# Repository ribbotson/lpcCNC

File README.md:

# lpcCNC Smoothieboard Derivative for CNC applications

This free open source derivative of the Smoothieboard is designed for CNC applications. It is intended for use with external stepper motor drivers. It features 13 digital open collector outputs, 8 digital inputs, 4 analog inputs, RS485 interface for spindle, 10V analog output for spindle, support for LCD screen, Ethernet, and power supply up to 40V.

## Content

This is a hardware project with PCB design file in Eagle. A 3D printable case ([Top]( http://a360.co/2vPnznS), [Bottom](http://a360.co/2j534xu)) design in Fusion360 is also provided. Example configuration files for Smoothieware and grbl-lpc are also provided.

## Authors

* **Richard Ibbotson**  

## License

Licensed under CERN OHL v.1.2 or later https://www.ohwr.org/documents/294 No warranty is provided for this documentation implied or otherwise.

## Acknowledgments

* All the folks at [rLab](http://www.rlab.org.uk) Reading Hackspace especially Toby
+ The Smoothieboard creators and the [Smoothieware](http://smoothieware.org/) team

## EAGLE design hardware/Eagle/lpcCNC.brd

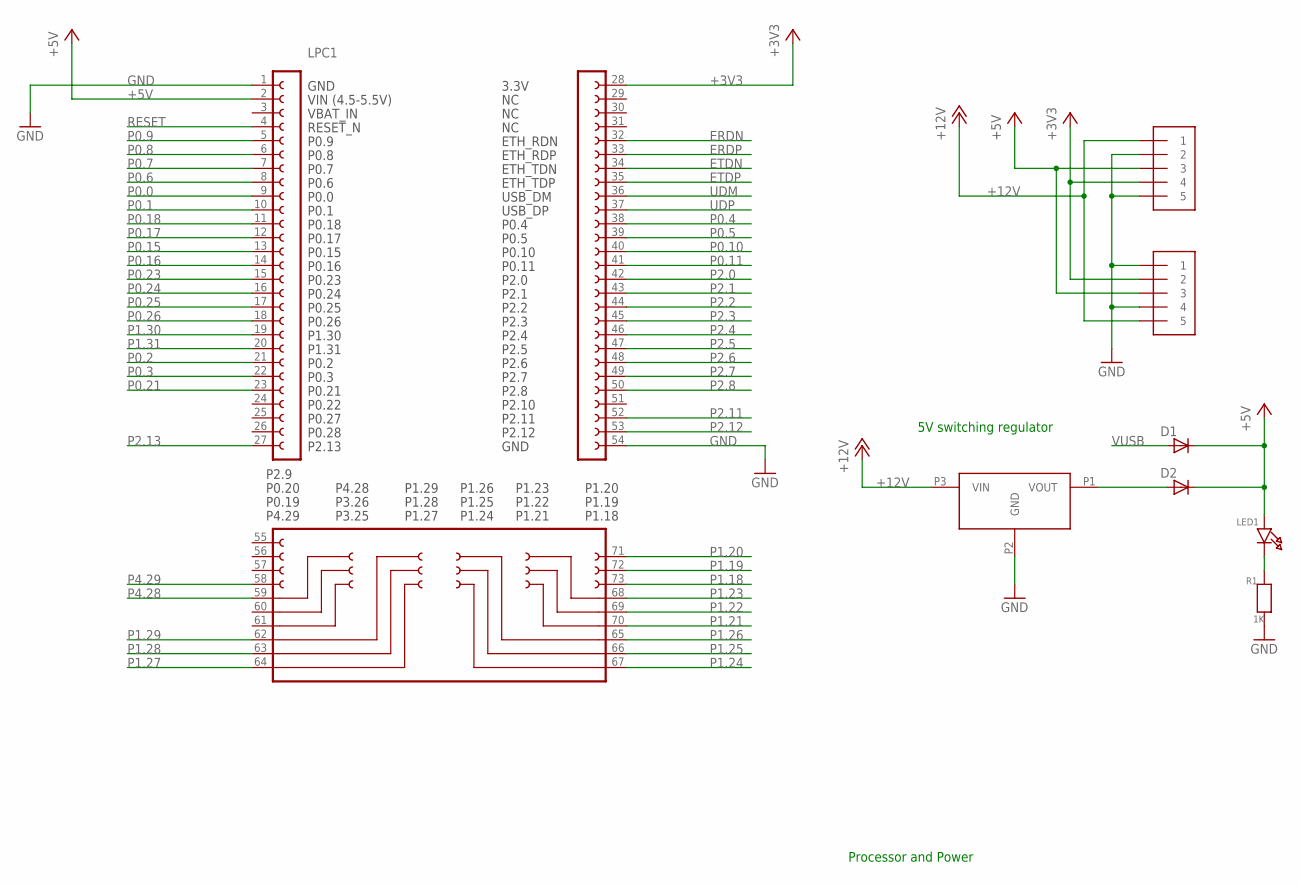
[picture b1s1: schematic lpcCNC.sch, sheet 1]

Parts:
D1, D2: DIODE-DO-214AC; DO-214AC
J1, J2: 1X5; 1X05-3.5MM
LED1: LED0603; CHIPLED_0603
LPC1: LPCXPRESSO_LPC1769
R1: 1K; 0603
VR1: 78SR

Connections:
+3V3: J1.4, J2.2, LPC1.28; also elsewhere on the board
+5V: D1.C, D2.C, J1.3, J2.3, LED1.A, LPC1.2; also elsewhere on the board
+12V: J1.1, J2.5, VR1.P3 (VIN); also elsewhere on the board
ERDN: LPC1.32; also elsewhere on the board
ERDP: LPC1.33; also elsewhere on the board
ETDN: LPC1.34; also elsewhere on the board
ETDP: LPC1.35; also elsewhere on the board
GND: J1.2, J1.5, J2.1, J2.4, LPC1.1, LPC1.54, R1.1, VR1.P2 (GND); also elsewhere on the board
unnamed: D2.A, VR1.P1 (VOUT)
unnamed: LED1.C, R1.2
P0.0: LPC1.9; also elsewhere on the board
P0.1: LPC1.10; also elsewhere on the board
P0.2: LPC1.21; also elsewhere on the board
P0.3: LPC1.22; also elsewhere on the board
P0.4: LPC1.38; also elsewhere on the board
P0.5: LPC1.39; also elsewhere on the board
P0.6: LPC1.8; also elsewhere on the board
P0.7: LPC1.7; also elsewhere on the board
P0.8: LPC1.6; also elsewhere on the board
P0.9: LPC1.5; also elsewhere on the board
P0.10: LPC1.40; also elsewhere on the board
P0.11: LPC1.41; also elsewhere on the board
P0.15: LPC1.13; also elsewhere on the board
P0.16: LPC1.14; also elsewhere on the board
P0.17: LPC1.12; also elsewhere on the board
P0.18: LPC1.11; also elsewhere on the board
P0.21: LPC1.23; also elsewhere on the board
P0.23: LPC1.15; also elsewhere on the board
P0.24: LPC1.16; also elsewhere on the board
P0.25: LPC1.17; also elsewhere on the board
P0.26: LPC1.18; also elsewhere on the board
P1.18: LPC1.73; also elsewhere on the board
P1.19: LPC1.72; also elsewhere on the board
P1.20: LPC1.71; also elsewhere on the board
P1.21: LPC1.70; also elsewhere on the board
P1.22: LPC1.69; also elsewhere on the board
P1.23: LPC1.68; also elsewhere on the board
P1.24: LPC1.67; also elsewhere on the board
P1.25: LPC1.66; also elsewhere on the board
P1.26: LPC1.65; also elsewhere on the board
P1.27: LPC1.64; also elsewhere on the board
P1.28: LPC1.63; also elsewhere on the board
P1.29: LPC1.62; also elsewhere on the board
P1.30: LPC1.19; also elsewhere on the board
P1.31: LPC1.20; also elsewhere on the board
P2.0: LPC1.42; also elsewhere on the board
P2.1: LPC1.43; also elsewhere on the board
P2.2: LPC1.44; also elsewhere on the board
P2.3: LPC1.45; also elsewhere on the board
P2.4: LPC1.46; also elsewhere on the board
P2.5: LPC1.47; also elsewhere on the board
P2.6: LPC1.48; also elsewhere on the board
P2.7: LPC1.49; also elsewhere on the board
P2.8: LPC1.50; also elsewhere on the board
P2.11: LPC1.52; also elsewhere on the board
P2.12: LPC1.53; also elsewhere on the board
P2.13: LPC1.27; also elsewhere on the board
P4.28: LPC1.59; also elsewhere on the board
P4.29: LPC1.58; also elsewhere on the board
RESET: LPC1.4; also elsewhere on the board
UDM: LPC1.36; also elsewhere on the board
UDP: LPC1.37; also elsewhere on the board
VUSB: D1.A; also elsewhere on the board

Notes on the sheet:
Processor and Power
5V switching regulator

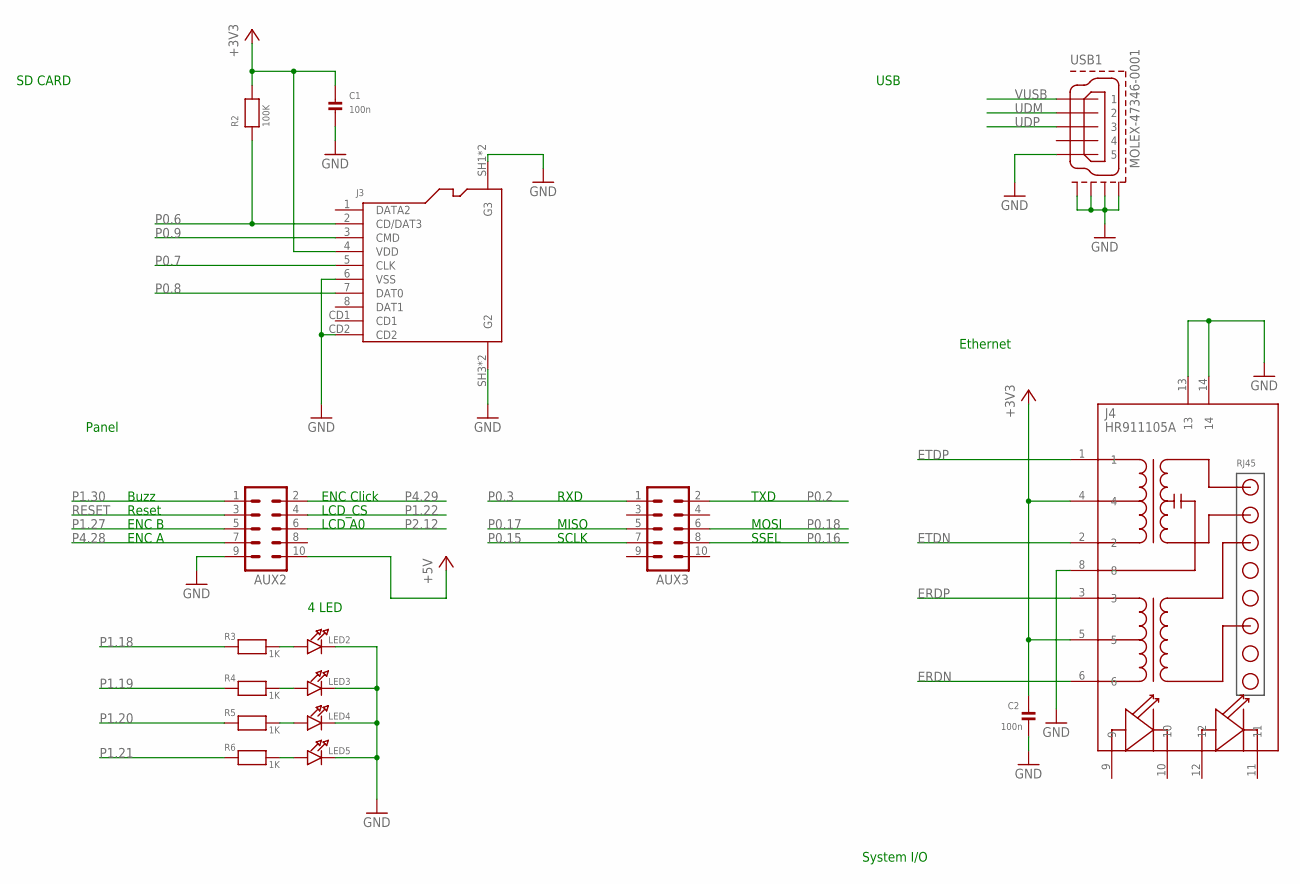
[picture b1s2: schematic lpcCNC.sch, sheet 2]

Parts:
AUX2, AUX3: ML10
C1, C2: 100n; 0603
J3: AMPHENOL_114-00841-68
J4: HR911105A
LED2, LED3, LED4, LED5: LED0603; CHIPLED_0603
R2: 100K; 0603
R3, R4, R5, R6: 1K; 0603
USB1: MOLEX-47346-0001; MOLEX-47364-0001

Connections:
+3V3: C1.1, C2.1, J3.4 (VDD), J4.4, J4.5, R2.2; also elsewhere on the board
+5V: AUX2.10; also elsewhere on the board
ERDN: J4.6; also elsewhere on the board
ERDP: J4.3; also elsewhere on the board
ETDN: J4.2; also elsewhere on the board
ETDP: J4.1; also elsewhere on the board
GND: AUX2.9, C1.2, C2.2, J3.6 (VSS), J3.CD2, J3.SH1 (G3), J3.SH2 (G3), J3.SH3 (G2), J3.SH4 (G2), J4.8, J4.13, J4.14, LED2.C, LED3.C, LED4.C, LED5.C, USB1.5, USB1.GND1, USB1.GND2, USB1.GND3, USB1.GND4; also elsewhere on the board
unnamed: LED2.A, R3.2
unnamed: LED3.A, R4.2
unnamed: LED4.A, R5.2
unnamed: LED5.A, R6.2
P0.2: AUX3.2; also elsewhere on the board
P0.3: AUX3.1; also elsewhere on the board
P0.6: J3.2 (CD/DAT3), R2.1; also elsewhere on the board
P0.7: J3.5 (CLK); also elsewhere on the board
P0.8: J3.7 (DAT0); also elsewhere on the board
P0.9: J3.3 (CMD); also elsewhere on the board
P0.15: AUX3.7; also elsewhere on the board
P0.16: AUX3.8; also elsewhere on the board
P0.17: AUX3.5; also elsewhere on the board
P0.18: AUX3.6; also elsewhere on the board
P1.18: R3.1; also elsewhere on the board
P1.19: R4.1; also elsewhere on the board
P1.20: R5.1; also elsewhere on the board
P1.21: R6.1; also elsewhere on the board
P1.22: AUX2.4; also elsewhere on the board
P1.27: AUX2.5; also elsewhere on the board
P1.30: AUX2.1; also elsewhere on the board
P2.12: AUX2.6; also elsewhere on the board
P4.28: AUX2.7; also elsewhere on the board
P4.29: AUX2.2; also elsewhere on the board
RESET: AUX2.3; also elsewhere on the board
UDM: USB1.2; also elsewhere on the board
UDP: USB1.3; also elsewhere on the board
VUSB: USB1.1; also elsewhere on the board

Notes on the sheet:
System I/O
Ethernet
USB
SD CARD
Panel
4 LED
ENC Click
LCD_CS
LCD A0
Reset
ENC A
ENC B
Buzz
TXD
RXD
MISO
SCLK
MOSI
SSEL

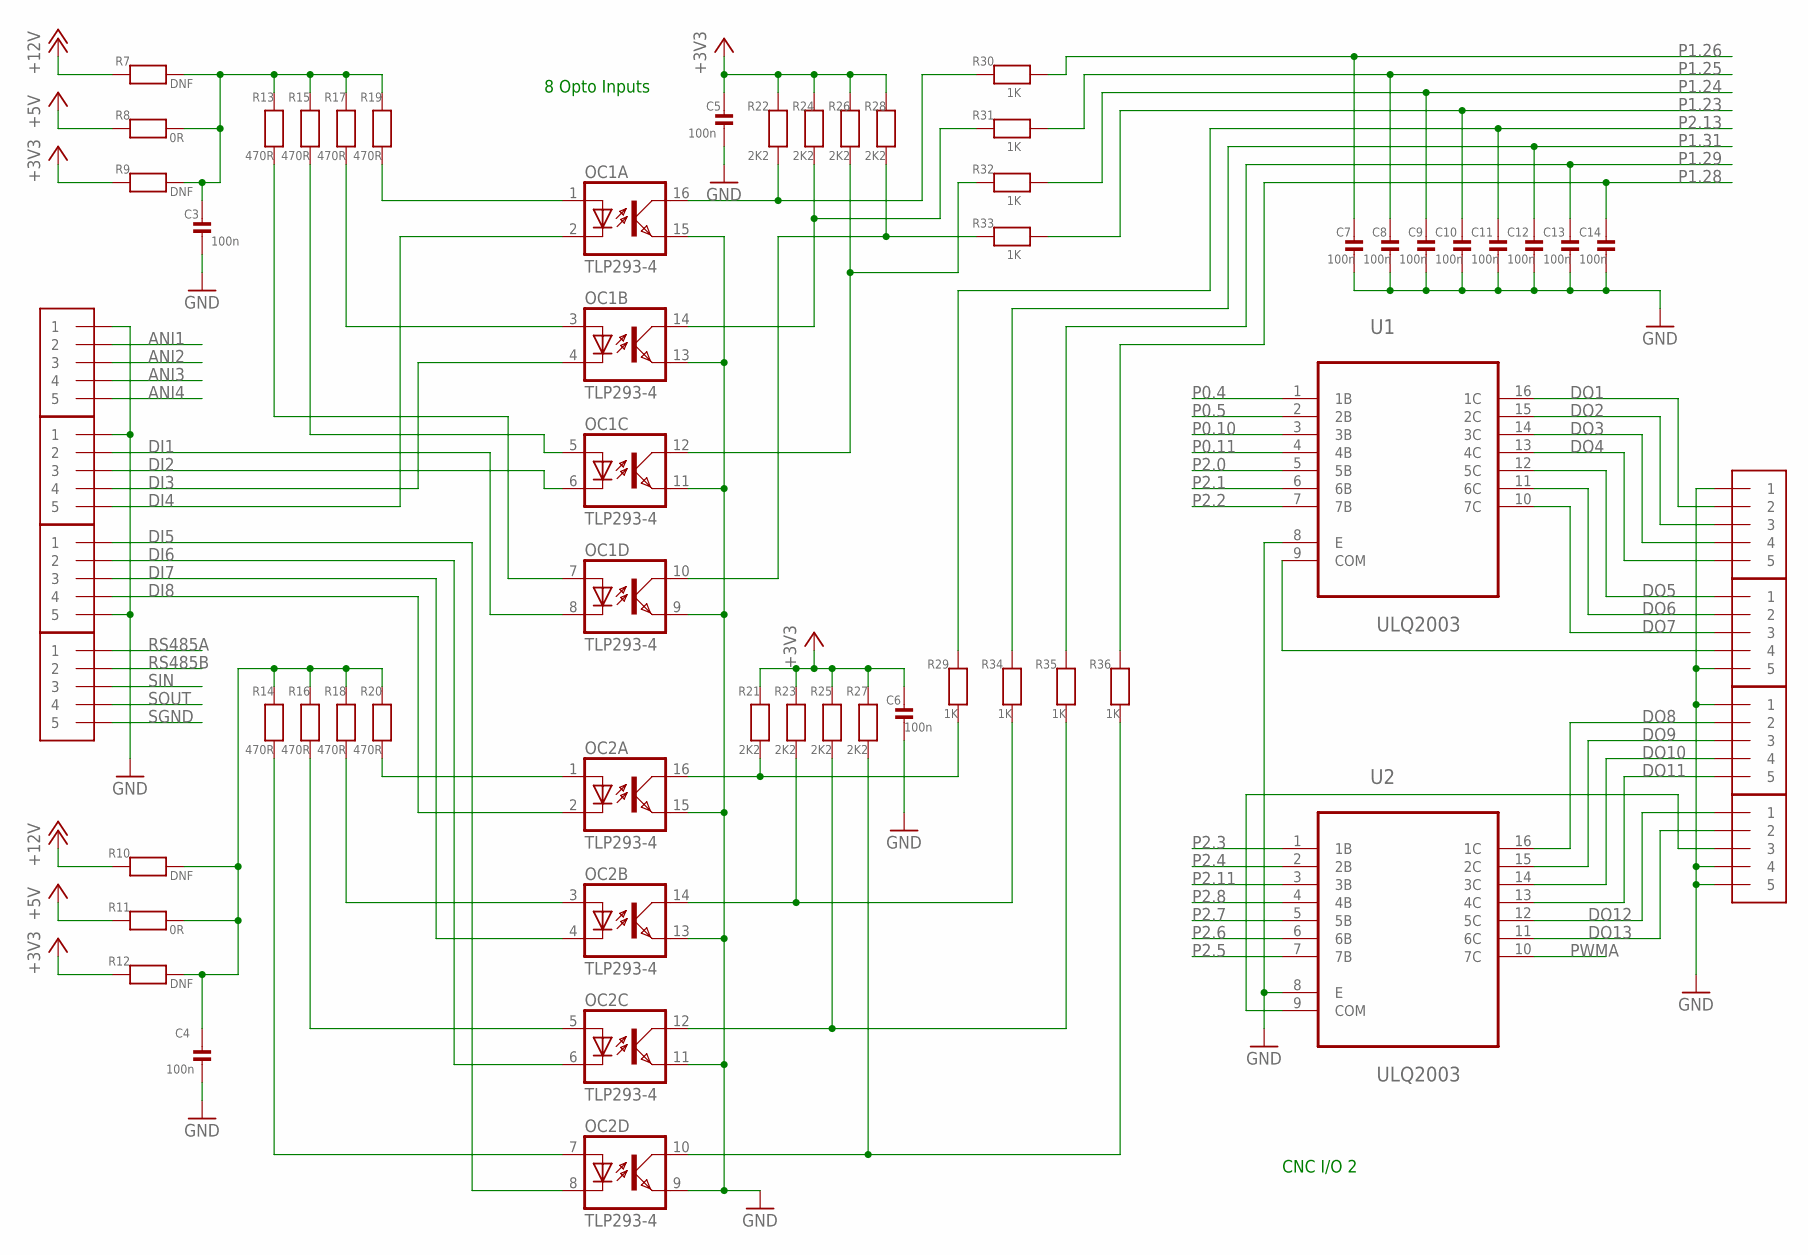
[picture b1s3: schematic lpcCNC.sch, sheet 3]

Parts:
C3, C4, C5, C6, C7, C8, C9, C10, C11, C12, C13, C14: 100n; 0603
J5, J6, J7, J8, J9, J10, J11, J12: 1X5; 1X05-3.5MM
OC1, OC2: TLP293-4; MINI-FLAT-16
R7, R9, R10, R12: DNF; 0603
R8, R11: 0R; 0603
R13, R14, R15, R16, R17, R18, R19, R20: 470R; 0603
R21, R22, R23, R24, R25, R26, R27, R28: 2K2; 0603
R29, R30, R31, R32, R33, R34, R35, R36: 1K; 0603
U1, U2: ULQ2003; SOIC127P600X175-16N

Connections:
+3V3: C5.1, C6.1, R9.2, R12.2, R21.2, R22.2, R23.2, R24.2, R25.2, R26.2, R27.2, R28.2; also elsewhere on the board
+5V: R8.2, R11.2; also elsewhere on the board
+12V: R7.2, R10.2; also elsewhere on the board
ANI1: J5.2; also elsewhere on the board
ANI2: J5.3; also elsewhere on the board
ANI3: J5.4; also elsewhere on the board
ANI4: J5.5; also elsewhere on the board
DI1: J6.2, OC1.8 (C)
DI2: J6.3, OC1.6 (C)
DI3: J6.4, OC1.4 (C)
DI4: J6.5, OC1.2 (C)
DI5: J7.1, OC2.8 (C)
DI6: J7.2, OC2.6 (C)
DI7: J7.3, OC2.4 (C)
DI8: J7.4, OC2.2 (C)
DO1: J9.2, U1.16 (1C)
DO2: J9.3, U1.15 (2C)
DO3: J9.4, U1.14 (3C)
DO4: J9.5, U1.13 (4C)
DO5: J10.1, U1.12 (5C)
DO6: J10.2, U1.11 (6C)
DO7: J10.3, U1.10 (7C)
DO8: J11.2, U2.16 (1C)
DO9: J11.3, U2.15 (2C)
DO10: J11.4, U2.14 (3C)
DO11: J11.5, U2.13 (4C)
DO12: J12.1, U2.12 (5C)
DO13: J12.2, U2.11 (6C)
GND: C3.2, C4.2, C5.2, C6.2, C7.2, C8.2, C9.2, C10.2, C11.2, C12.2, C13.2, C14.2, J5.1, J6.1, J7.5, J9.1, J10.5, J11.1, J12.4, J12.5, OC1.9 (EMIT), OC1.11 (EMIT), OC1.13 (EMIT), OC1.15 (EMIT), OC2.9 (EMIT), OC2.11 (EMIT), OC2.13 (EMIT), OC2.15 (EMIT), U1.8 (E), U2.8 (E); also elsewhere on the board
unnamed: J10.4, U1.9 (COM)
unnamed: J12.3, U2.9 (COM)
unnamed: C3.1, R7.1, R8.1, R9.1, R13.2, R15.2, R17.2, R19.2
unnamed: OC2.1 (A), R20.1
unnamed: OC2.3 (A), R18.1
unnamed: OC2.5 (A), R16.1
unnamed: OC2.7 (A), R14.1
unnamed: C4.1, R10.1, R11.1, R12.1, R14.2, R16.2, R18.2, R20.2
unnamed: OC1.1 (A), R19.1
unnamed: OC1.3 (A), R17.1
unnamed: OC1.5 (A), R15.1
unnamed: OC1.7 (A), R13.1
unnamed: OC1.16 (COL), R22.1, R30.2
unnamed: OC1.14 (COL), R24.1, R31.2
unnamed: OC2.16 (COL), R21.1, R29.1
unnamed: OC2.14 (COL), R23.1, R34.1
unnamed: OC2.12 (COL), R25.1, R35.1
unnamed: OC2.10 (COL), R27.1, R36.1
unnamed: OC1.12 (COL), R26.1, R32.2
unnamed: OC1.10 (COL), R28.1, R33.2
P0.4: U1.1 (1B); also elsewhere on the board
P0.5: U1.2 (2B); also elsewhere on the board
P0.10: U1.3 (3B); also elsewhere on the board
P0.11: U1.4 (4B); also elsewhere on the board
P1.23: C10.1, R33.1; also elsewhere on the board
P1.24: C9.1, R32.1; also elsewhere on the board
P1.25: C8.1, R31.1; also elsewhere on the board
P1.26: C7.1, R30.1; also elsewhere on the board
P1.28: C14.1, R36.2; also elsewhere on the board
P1.29: C13.1, R35.2; also elsewhere on the board
P1.31: C12.1, R34.2; also elsewhere on the board
P2.0: U1.5 (5B); also elsewhere on the board
P2.1: U1.6 (6B); also elsewhere on the board
P2.2: U1.7 (7B); also elsewhere on the board
P2.3: U2.1 (1B); also elsewhere on the board
P2.4: U2.2 (2B); also elsewhere on the board
P2.5: U2.7 (7B); also elsewhere on the board
P2.6: U2.6 (6B); also elsewhere on the board
P2.7: U2.5 (5B); also elsewhere on the board
P2.8: U2.4 (4B); also elsewhere on the board
P2.11: U2.3 (3B); also elsewhere on the board
P2.13: C11.1, R29.2; also elsewhere on the board
PWMA: U2.10 (7C); also elsewhere on the board
RS485A: J8.1; also elsewhere on the board
RS485B: J8.2; also elsewhere on the board
SGND: J8.5; also elsewhere on the board
SIN: J8.3; also elsewhere on the board
SOUT: J8.4; also elsewhere on the board

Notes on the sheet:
CNC I/O 2
8 Opto Inputs

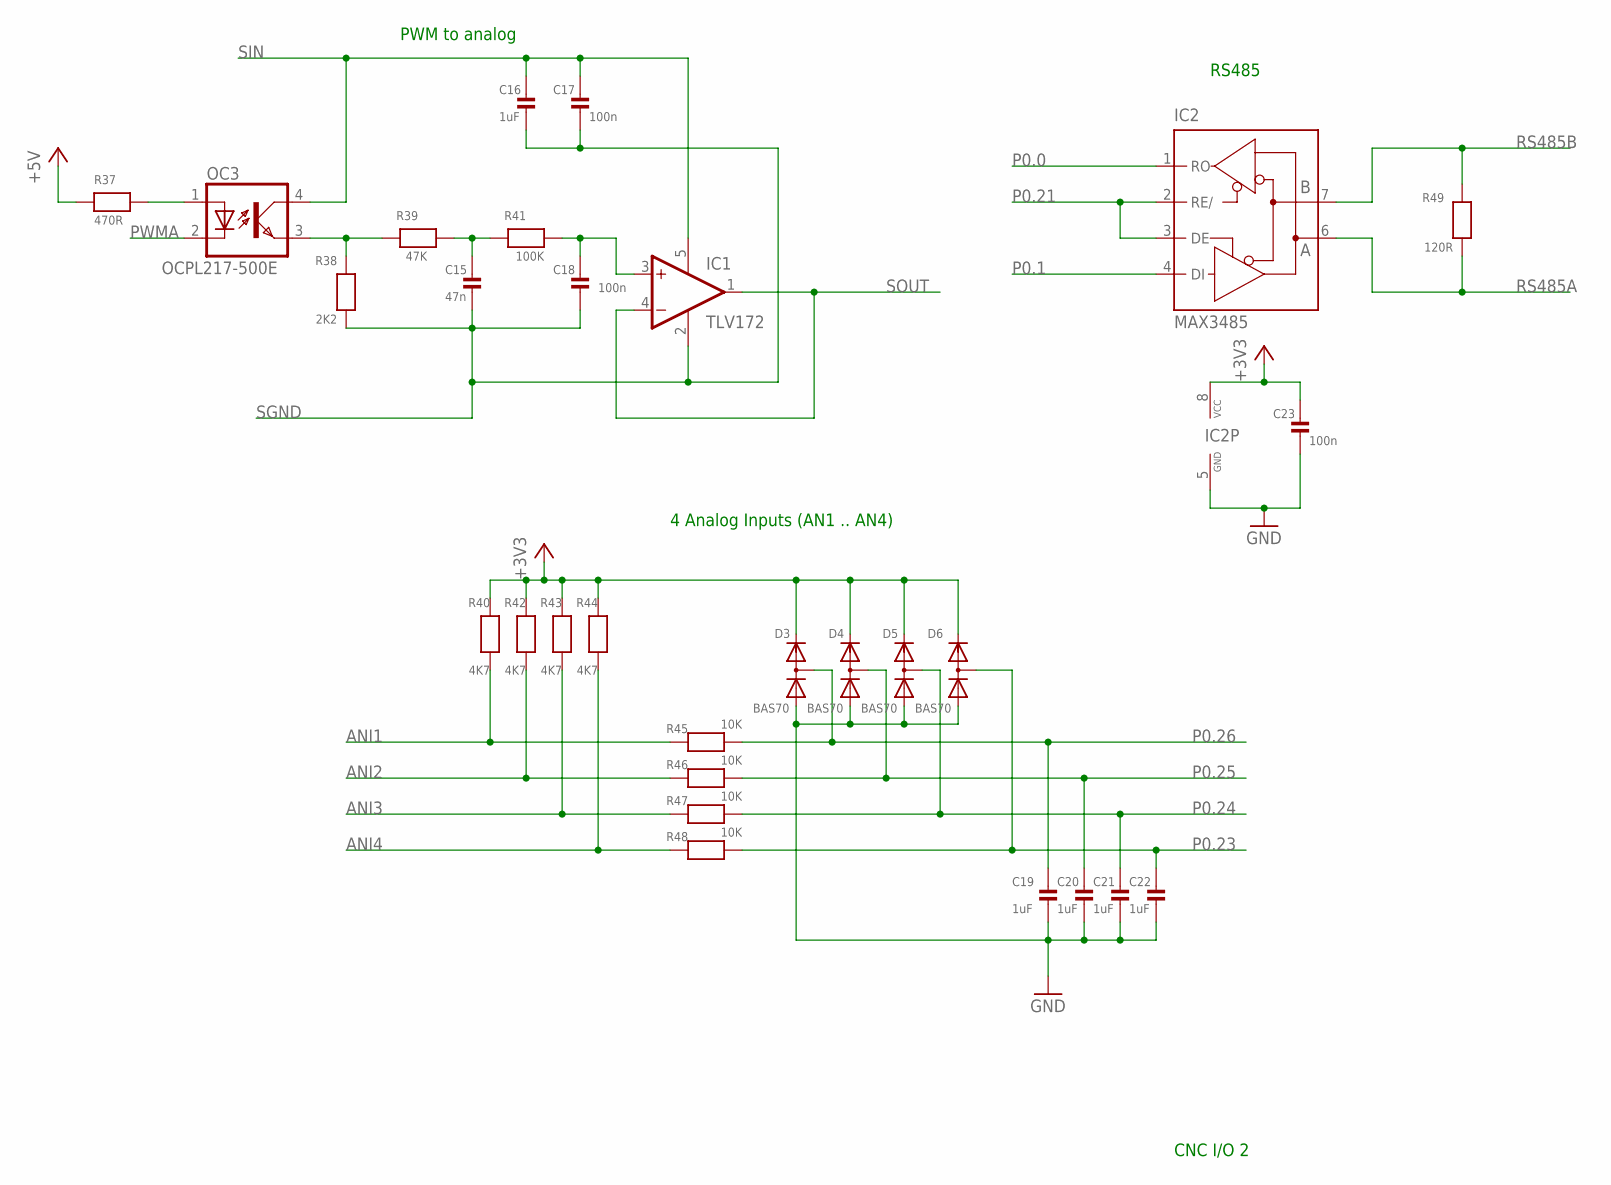
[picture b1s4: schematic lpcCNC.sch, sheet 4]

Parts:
C15: 47n; 0603
C16, C19, C20, C21, C22: 1uF; 0603
C17, C18, C23: 100n; 0603
D3, D4, D5, D6: BAS70; SOT23
IC1: TLV172; SOT23-5
IC2: MAX3485; SO08
OC3: OCPL217-500E; MINI-FLAT-4
R37: 470R; 0603
R38: 2K2; 0603
R39: 47K; 0603
R40, R42, R43, R44: 4K7; 0603
R41: 100K; 0603
R45, R46, R47, R48: 10K; 0603
R49: 120R; 0603

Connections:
+3V3: C23.1, D3.2 (C), D4.2 (C), D5.2 (C), D6.2 (C), IC2.8 (VCC), R40.2, R42.2, R43.2, R44.2; also elsewhere on the board
+5V: R37.1; also elsewhere on the board
ANI1: R40.1, R45.2; also elsewhere on the board
ANI2: R42.1, R46.2; also elsewhere on the board
ANI3: R43.1, R47.2; also elsewhere on the board
ANI4: R44.1, R48.2; also elsewhere on the board
GND: C19.2, C20.2, C21.2, C22.2, C23.2, D3.1 (A), D4.1 (A), D5.1 (A), D6.1 (A), IC2.5 (GND); also elsewhere on the board
unnamed: OC3.1 (A), R37.2
unnamed: OC3.3 (EMIT), R38.2, R39.2
unnamed: C15.1, R39.1, R41.2
unnamed: C18.1, IC1.3 (+IN), R41.1
P0.0: IC2.1 (RO); also elsewhere on the board
P0.1: IC2.4 (DI); also elsewhere on the board
P0.21: IC2.2 (RE/), IC2.3 (DE); also elsewhere on the board
P0.23: C22.1, D6.3 (AC), R48.1; also elsewhere on the board
P0.24: C21.1, D5.3 (AC), R47.1; also elsewhere on the board
P0.25: C20.1, D4.3 (AC), R46.1; also elsewhere on the board
P0.26: C19.1, D3.3 (AC), R45.1; also elsewhere on the board
PWMA: OC3.2 (C); also elsewhere on the board
RS485A: IC2.6 (A), R49.1; also elsewhere on the board
RS485B: IC2.7 (B), R49.2; also elsewhere on the board
SGND: C15.2, C16.2, C17.2, C18.2, IC1.2 (V-), R38.1; also elsewhere on the board
SIN: C16.1, C17.1, IC1.5 (V+), OC3.4 (COL); also elsewhere on the board
SOUT: IC1.1 (OUT), IC1.4 (-IN); also elsewhere on the board

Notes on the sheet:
CNC I/O 2
4 Analog Inputs (AN1 .. AN4)
PWM to analog
RS485

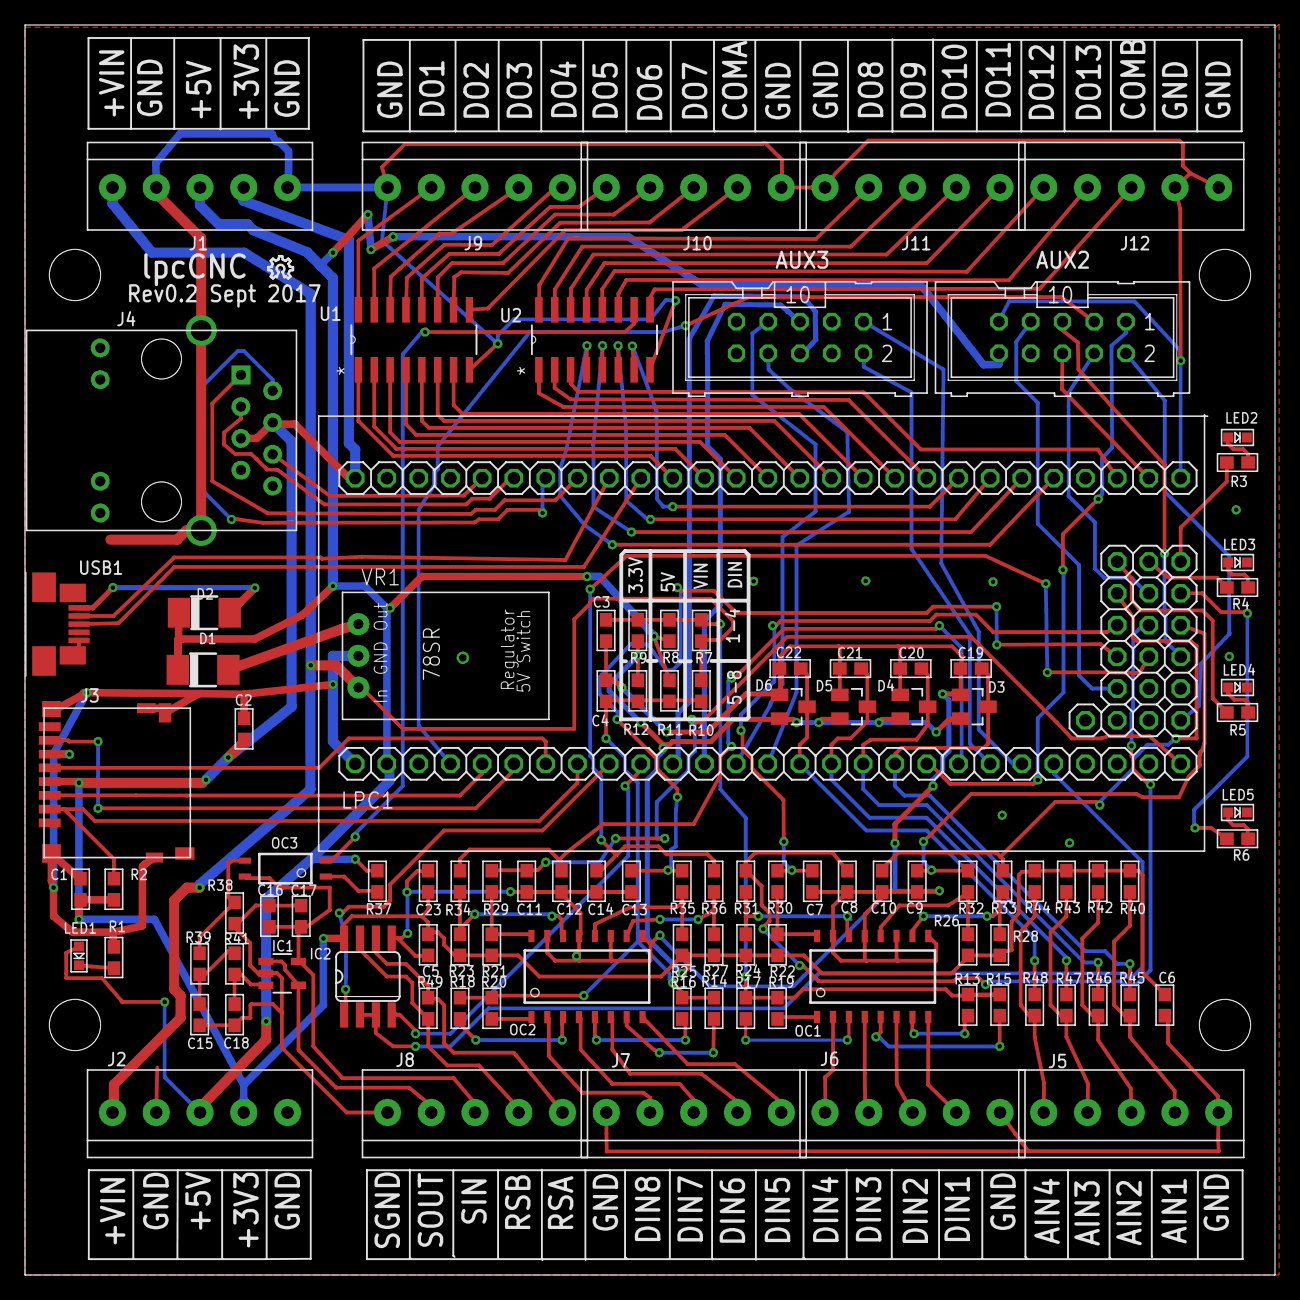
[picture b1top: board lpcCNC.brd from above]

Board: 2 copper layers, 100.0 x 100.0 mm, 108 parts (0 on the bottom side), 122 nets.

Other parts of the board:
U$1: OSHW_8X70_NOTEXT

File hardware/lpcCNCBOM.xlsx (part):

Column1 | Column2 | Column3 | Column4 | Column5 | Column6 | Column7 | Column8 | Column9
Part | Value | Device | Package | Description | Manufacturer | Manufacturer Part Number | Supplier | Supplier Part number
AUX2 | 10 Way | Header | 10 Way | 10 Way Boxed Header | TruConnect | DS1013-10 | Rapid | 19-0033
AUX3 | 10 Way | Header | ML10 | 10 Way Boxed Header | TruConnect | DS1013-10 | Rapid | 19-0033
C1 | 100n | Cap Ceramic 50V | 0603 | Ceramic Capacitors | Murata | GRM188F51H104ZA01D | RS | 723-5534
C2 | 100n | Cap Ceramic 50V | 0603 | Ceramic Capacitors | Murata | GRM188F51H104ZA01D | RS | 723-5534
C3 | 100n | Cap Ceramic 50V | 0603 | Ceramic Capacitors | Murata | GRM188F51H104ZA01D | RS | 723-5534
C4 | 100n | Cap Ceramic 50V | 0603 | Ceramic Capacitors | Murata | GRM188F51H104ZA01D | RS | 723-5534
C5 | 100n | Cap Ceramic 50V | 0603 | Ceramic Capacitors | Murata | GRM188F51H104ZA01D | RS | 723-5534
C6 | 100n | Cap Ceramic 50V | 0603 | Ceramic Capacitors | Murata | GRM188F51H104ZA01D | RS | 723-5534
C7 | 100n | Cap Ceramic 50V | 0603 | Ceramic Capacitors | Murata | GRM188F51H104ZA01D | RS | 723-5534
C8 | 100n | Cap Ceramic 50V | 0603 | Ceramic Capacitors | Murata | GRM188F51H104ZA01D | RS | 723-5534
C9 | 100n | Cap Ceramic 50V | 0603 | Ceramic Capacitors | Murata | GRM188F51H104ZA01D | RS | 723-5534
C10 | 100n | Cap Ceramic 50V | 0603 | Ceramic Capacitors | Murata | GRM188F51H104ZA01D | RS | 723-5534
C11 | 100n | Cap Ceramic 50V | 0603 | Ceramic Capacitors | Murata | GRM188F51H104ZA01D | RS | 723-5534
C12 | 100n | Cap Ceramic 50V | 0603 | Ceramic Capacitors | Murata | GRM188F51H104ZA01D | RS | 723-5534
C13 | 100n | Cap Ceramic 50V | 0603 | Ceramic Capacitors | Murata | GRM188F51H104ZA01D | RS | 723-5534
C14 | 100n | Cap Ceramic 50V | 0603 | Ceramic Capacitors | Murata | GRM188F51H104ZA01D | RS | 723-5534
C15 | 47n | Cap Ceramic 50V | 0603 | Ceramic Capacitors | Murata | GRM188B11E473KA01D | RS | 798-0332
C16 | 1uF | Cap Ceramic 25V | 0603 | Ceramic Capacitors | Murata | GRM188R61E105KA12D | RS | 723-5587
C17 | 100n | Cap Ceramic 50V | 0603 | Ceramic Capacitors | Murata | GRM188F51H104ZA01D | RS | 723-5534
C18 | 100n | Cap Ceramic 50V | 0603 | Ceramic Capacitors | Murata | GRM188F51H104ZA01D | RS | 723-5534
C19 | 1uF | Cap Ceramic 25V | 0603 | Ceramic Capacitors | Murata | GRM188R61E105KA12D | RS | 723-5587
C20 | 1uF | Cap Ceramic 25V | 0603 | Ceramic Capacitors | Murata | GRM188R61E105KA12D | RS | 723-5587
C21 | 1uF | Cap Ceramic 25V | 0603 | Ceramic Capacitors | Murata | GRM188R61E105KA12D | RS | 723-5587
C22 | 1uF | Cap Ceramic 25V | 0603 | Ceramic Capacitors | Murata | GRM188R61E105KA12D | RS | 723-5587
C23 | 100n | Cap Ceramic 50V | 0603 | Ceramic Capacitors | Murata | GRM188F51H104ZA01D | RS | 723-5534
D1 | MBRA140 | DIODE-DO-214AC | DO-214AC | Schottky Power Diode | ON Semi | MBRA140T3G | RS | 625-5650
D2 | MBRA140 | DIODE-DO-214AC | DO-214AC | Schottky Power Diode | ON Semi | MBRA140T3G | RS | 625-5650
D3 | BAS70-04 | DIODE_2CACA-SOT23 | SOT23 | Dual Schottky Diode | Multicomp | BAS70-04 | Farnell | 179-7835
D4 | BAS70-04 | DIODE_2CACA-SOT23 | SOT23 | Dual Schottky Diode | Multicomp | BAS70-04 | Farnell | 179-7835
D5 | BAS70-04 | DIODE_2CACA-SOT23 | SOT23 | Dual Schottky Diode | Multicomp | BAS70-04 | Farnell | 179-7835
D6 | BAS70-04 | DIODE_2CACA-SOT23 | SOT23 | Dual Schottky Diode | Multicomp | BAS70-04 | Farnell | 179-7835
IC1 | TLV172 | TLV172MF | SOT23-5 | Low Power Single Op Amp | Texas Instruments | TLV172IDBVR | Farnell | 267-7088
IC2 | MAX3485 | MAX481CSA | SO08 | RS485 Transceiver | Maxim | MAX3485ECSA+ | Farnell | 251-8816
J1 | 1X5 | 1X5 | 1X05-3.5MM | 3.5mm Pitch Screw Header | CamdenBoss | CTB3051/5BK | Rapid | 21-4708
J2 | 1X5 | 1X5 | 1X05-3.5MM | 3.5mm Pitch Screw Header | CamdenBoss | CTB3051/5BK | Rapid | 21-4708
J3 |  | AMPHENOL_114-00841-68 | AMPHENOL_114-00841-68 | Micro SD Card Holder | Amphenol | 114-00841-68 | Farnell | 266-6772
J4 | HR911105A | HR911105A | HR911105A | Ethernet Mag Jack | HanRun | HR911105A | eBay | HR911105A
J5 | 1X5 | 1X5 | 1X05-3.5MM | 3.5mm Pitch Screw Header | CamdenBoss | CTB3051/5BK | Rapid | 21-4708
J6 | 1X5 | 1X5 | 1X05-3.5MM | 3.5mm Pitch Screw Header | CamdenBoss | CTB3051/5BK | Rapid | 21-4708
J7 | 1X5 | 1X5 | 1X05-3.5MM | 3.5mm Pitch Screw Header | CamdenBoss | CTB3051/5BK | Rapid | 21-4708
J8 | 1X5 | 1X5 | 1X05-3.5MM | 3.5mm Pitch Screw Header | CamdenBoss | CTB3051/5BK | Rapid | 21-4708
J9 | 1X5 | 1X5 | 1X05-3.5MM | 3.5mm Pitch Screw Header | CamdenBoss | CTB3051/5BK | Rapid | 21-4708
J10 | 1X5 | 1X5 | 1X05-3.5MM | 3.5mm Pitch Screw Header | CamdenBoss | CTB3051/5BK | Rapid | 21-4708
J11 | 1X5 | 1X5 | 1X05-3.5MM | 3.5mm Pitch Screw Header | CamdenBoss | CTB3051/5BK | Rapid | 21-4708
J12 | 1X5 | 1X5 | 1X05-3.5MM | 3.5mm Pitch Screw Header | CamdenBoss | CTB3051/5BK | Rapid | 21-4708
J13 | 27 pin | 2.54mm Pitch Female | Pin Header | Female Pin Header |  | 40 Pin strip | eBay
J14 | 27 pin | 2.54mm Pitch Female | Pin Header | Female Pin Header |  | 40 Pin strip | eBay
J15 | 4 pin | 2.54mm Pitch Female | Pin Header | Female Pin Header |  | 40 Pin strip | eBay
J16 | 3 pin | 2.54mm Pitch Female | Pin Header | Female Pin Header |  | 40 Pin strip | eBay
J17 | 3 pin | 2.54mm Pitch Female | Pin Header | Female Pin Header |  | 40 Pin strip | eBay
J18 | 3 pin | 2.54mm Pitch Female | Pin Header | Female Pin Header |  | 40 Pin strip | eBay
J19 | 27 pin | 2.54mm Pitch Male | Pin Header | Male Pin Header |  | 40 Pin strip | eBay
J20 | 27 pin | 2.54mm Pitch Male | Pin Header | Male Pin Header |  | 40 Pin strip | eBay
J21 | 4 pin | 2.54mm Pitch Male | Pin Header | Male Pin Header |  | 40 Pin strip | eBay
J22 | 3 pin | 2.54mm Pitch Male | Pin Header | Male Pin Header |  | 40 Pin strip | eBay
J23 | 3 pin | 2.54mm Pitch Male | Pin Header | Male Pin Header |  | 40 Pin strip | eBay
J24 | 3 pin | 2.54mm Pitch Male | Pin Header | Male Pin Header |  | 40 Pin strip | eBay
LED1 | Green |  | LED 0603 | SMT LED | Osram | LP L296-J2L2-25 | RS | 915-4768
LED2 | Green |  | LED 0603 | SMT LED | Osram | LP L296-J2L2-25 | RS | 915-4768
LED3 | Green |  | LED 0603 | SMT LED | Osram | LP L296-J2L2-25 | RS | 915-4768
LED4 | Green |  | LED 0603 | SMT LED | Osram | LP L296-J2L2-25 | RS | 915-4768
LED5 | Green |  | LED 0603 | SMT LED | Osram | LP L296-J2L2-25 | RS | 915-4768
LPC1 | LPC Expresso1769 | LPCXPRESSO_LPC1769 | Custom | Processor Module | NXP | OM13085UL | Farnell | 252-3091
OC1 | TLP293-4 | TLP293-4 | SOIC16 | Quad Optocoupler | Toshiba | TLP293-4 | Farnell | 252-4319
OC2 | TLP293-4 | TLP293-4 | SOIC16 | Quad Optocoupler | Toshiba | Toshiba | Farnell | 252-4319
OC3 | ACPL217-500E | ACPL217 | SOIC4 | Optocoupler | Avago | ACPL-217-500E | Rapid | 75-0230
R1 | 1K | RESISTOR0603 | 0603 | Resistors | Panasonic | ERJ3EKF1001V | RS | 873-9223
R2 | 100K | RESISTOR0603 | 0603 | Resistors | Panasonic | ERJU03F1003V | RS | 873-9220
R3 | 1K | RESISTOR0603 | 0603 | Resistors | Panasonic | ERJ3EKF1001V | RS | 873-9223
R4 | 1K | RESISTOR0603 | 0603 | Resistors | Panasonic | ERJ3EKF1001V | RS | 873-9223
R5 | 1K | RESISTOR0603 | 0603 | Resistors | Panasonic | ERJ3EKF1001V | RS | 873-9223
R6 | 1K | RESISTOR0603 | 0603 | Resistors | Panasonic | ERJ3EKF1001V | RS | 873-9223
R7 | Do Not Fit | RESISTOR0603 | 0603 | Resistors | Vishay | CRCW06030000Z0EB | RS | 678-9670
R8 | 0R | RESISTOR0603 | 0603 | Resistors | Vishay | CRCW06030000Z0EB | RS | 678-9670
R9 | Do Not Fit | RESISTOR0603 | 0603 | Resistors | Vishay | CRCW06030000Z0EB | RS | 678-9670
R10 | Do Not Fit | RESISTOR0603 | 0603 | Resistors | Vishay | CRCW06030000Z0EB | RS | 678-9670
R11 | 0R | RESISTOR0603 | 0603 | Resistors | Vishay | CRCW06030000Z0EB | RS | 678-9670
R12 | Do Not Fit | RESISTOR0603 | 0603 | Resistors | Vishay | CRCW06030000Z0EB | RS | 678-9670
R13 | 470R | RESISTOR0603 | 0603 | Resistors | Panasonic | ERJPA3F4700V | RS | 862-6966
R14 | 470R | RESISTOR0603 | 0603 | Resistors | Panasonic | ERJPA3F4700V | RS | 862-6966
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
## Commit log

2017-09-07 :octocat: Added .gitattributes & .gitignore files
2017-09-07 Initial File Upload
    Add Eagle files
2017-09-07 Add readme
2017-09-07 Add files for case
    Fusion 360 archive and STL files
2017-09-10 Add Smoothie confog for Shapeoko and pin document
2018-02-26 Fusion 360 Post Processor

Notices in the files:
parts and their libraries:
microbuilder: This work is placed in the public domain, and may be freely used for commercial and non-commercial work with the following conditions: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
